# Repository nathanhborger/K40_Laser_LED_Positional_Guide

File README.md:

# K40 Laser LED Positional Guide

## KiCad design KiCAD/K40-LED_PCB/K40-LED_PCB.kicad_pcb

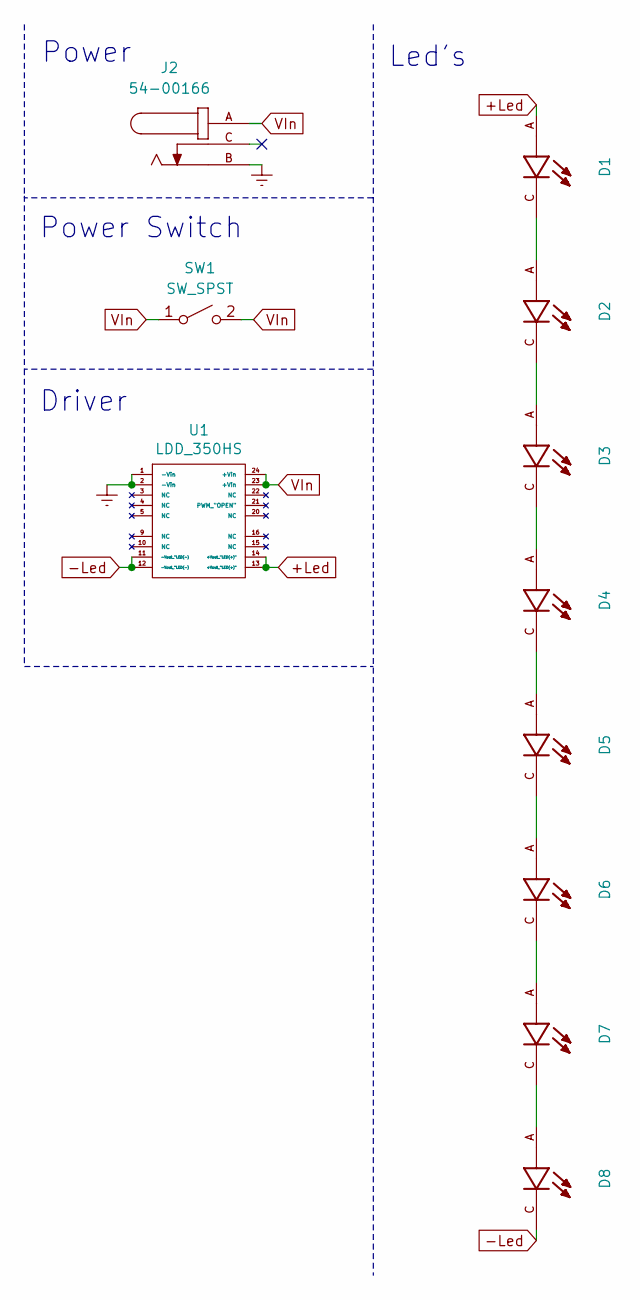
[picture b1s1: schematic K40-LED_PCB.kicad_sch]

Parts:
D1, D2, D3, D4, D5, D6, D7, D8: LTST-C190KGKT; Cree_MX3AWT-A1-R250-000BE3
J2: 54-00166; TENSILITY_54-00166; PARTREV A
SW1: SW_SPST; PinHeader_1x02_P2.00mm_Vertical
U1: LDD_350HS; LDD-350HS

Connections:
+Led: D1.A, U1.13 (+Vout_"LED(+)"), U1.14 (+Vout_"LED(+)")
-Led: D8.C, U1.11 (-Vout_"LED(-)), U1.12 (-Vout_"LED(-))
Earth: D1.65, D2.65, D3.65, D4.65, D5.65, D6.65, D7.65, D8.65, J2.B, U1.1 (-Vin), U1.2 (-Vin)
unnamed: D1.C, D2.A
unnamed: D2.C, D3.A
unnamed: D3.C, D4.A
unnamed: D4.C, D5.A
unnamed: D5.C, D6.A
unnamed: D6.C, D7.A
unnamed: D7.C, D8.A
VIn: J2.A, SW1.1 (A), SW1.2 (B), U1.23 (+Vin), U1.24 (+Vin)

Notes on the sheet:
Power
Led's
Driver
Power Switch

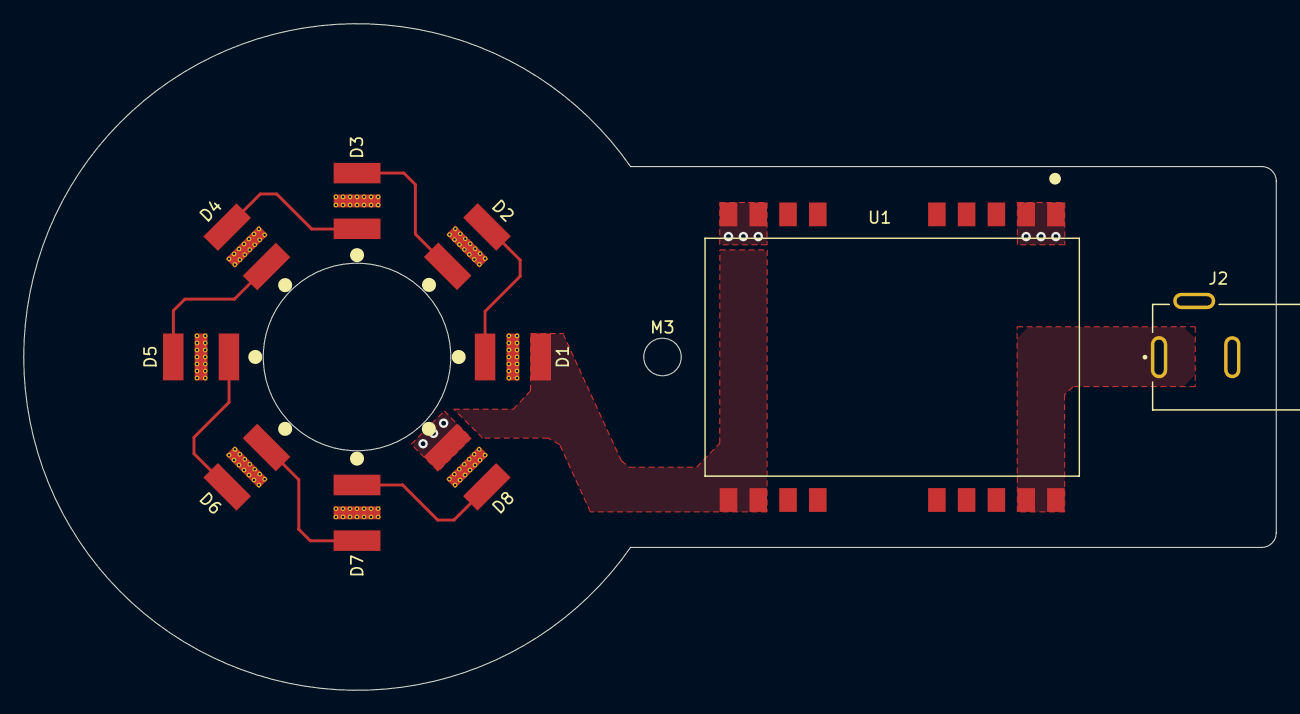
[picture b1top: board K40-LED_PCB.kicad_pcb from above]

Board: 2 copper layers, 106.9 x 56.9 mm, 11 parts (0 on the bottom side), 11 nets.

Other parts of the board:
M3: MountingHole_3.2mm_M3

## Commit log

2024-04-14 PCB Updates : Placement Done
2024-05-27 Finalizing PCB. Get Checked.
2024-05-27 PCB updates. Finalized
2024-05-27 Blender Scenes and Rendering finished.
